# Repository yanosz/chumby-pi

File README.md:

# Turn a Raspberry Pi into a Chumby

> **Heads up:** this is an AI-generated hobby project, built for fun and
> not actively maintained. No support and no warranty — but it works, and
> it's yours to tinker with.

Remember the [Chumby](https://en.wikipedia.org/wiki/Chumby)? The little
squeezable Wi-Fi gadget that showed widgets and woke you up in the
morning, until its servers went dark. This project brings its control
panel back to life on a Raspberry Pi with a small touchscreen — running
the **real** `controlpanel.swf` from the original firmware, unmodified.

It does that with [chumby-ruffle](https://github.com/yanosz/chumby-ruffle),
a fork of the [Ruffle](https://ruffle.rs) Flash player that pretends to be
Chumby hardware. The panel never notices the difference: the clock ticks,
alarms ring, internet radio streams, and your volume and settings stick
around between reboots.

## What you'll need

- A **Raspberry Pi with a small touchscreen.** The reference build is a
  Pi 3B+ with a 3.5″ SPI display and a USB audio dongle; other displays
  and sound devices work too — see [docs/hardware.md](docs/hardware.md).
- The **Chumby firmware files** — `controlpanel.swf`, the intro, and
  the alarm tones. These are copyrighted and **not included here**:
  pull them from your own Chumby's backup, or let
  `chumby-download-firmware` (part of the package) fetch them all from
  Chumby's still-running servers — it asks first and shows what it
  downloads. Widgets are optional; without any, the panel is a clock.
  Which file goes where is in [docs/setup.md](docs/setup.md).

## Try it on your computer first

Before touching the Pi, you can run the panel in a window on any Linux
machine:

```sh
git clone --recursive https://github.com/yanosz/chumby-pi.git
cd chumby-pi
# drop controlpanel.swf into ruffle/swf-assets/ first — see docs/setup.md
cd ruffle && cargo build -p ruffle_desktop
./run-controlpanel.sh
```

Your PC has no bend sensor (the squeeze the Chumby is famous for), so
long-press with the mouse to fake it.

## Put it on the Pi

The full walkthrough — flashing the card, installing the packages, and
setting up the boot-to-panel kiosk — lives in
**[docs/setup.md](docs/setup.md)**. Follow it to the end and the Pi boots
straight into the control panel, no desktop in sight.

## The display (SPI TFT)

The reference display is a 3.5″ 480×320 ILI9486 SPI panel with XPT2046
resistive touch — sold as "Waveshare 3.5inch RPi LCD (B)" and as many
clones. Two things matter:

- **Skip the vendor's driver instructions.** Overlays like
  `waveshare35b-v2` (and the wiki's `hdmi_*` block) use the old fbtft
  framebuffer driver, which Wayland cannot see — the kiosk then fails
  with *"Found 0 GPUs, cannot create backend"*. The mainline kernel
  already ships a proper DRM driver for this panel.
- Append this to `/boot/firmware/config.txt` and reboot:

  ```
  dtparam=spi=on
  dtoverlay=piscreen,speed=24000000,rotate=0,drm,swapxy=on,invy=on
  ```

  `drm` selects the mainline driver; `swapxy` and `invy` align the
  touchscreen axes with the landscape screen.

That's all: the kiosk finds the SPI panel by itself, on any Pi model.
**HDMI and DSI displays** (like the official 7″ touchscreen) **need no
configuration at all** — the overlay lines above are only for SPI
panels, which the Pi cannot detect on its own. To pin a specific
display, set `WLR_DRM_DEVICES` in `/etc/default/chumby-player`.

## What's in this repo

| Directory | What's inside |
|-----------|---------------|
| `ruffle/` | the chumby-ruffle player, as a git submodule. It brings its own `fixtures/` (the fake Chumby the panel talks to), the desktop launcher, and where the copyrighted firmware files go |
| `pkg/` | the Debian packages and the kiosk service that boots to the panel |
| `docs/` | the setup and hardware guides — **start with [docs/setup.md](docs/setup.md)** |

There's also a `claude-docs/` folder with the engineering record — what
this thing has to do, how it's put together, and how to work on it. Handy
if you want to know *why* something works, but not needed to use it. The
player has its own record, in the `ruffle/` submodule.

A `yoga-widget/` folder, where present, is a separate project — chumby-yoga,
a video widget for the original chumby hardware. It is not part of this repo
(ignored here) and is documented in its own repository.

Likewise `rust-remote/` (chumby-rust-remote): a separate project with its own git
repository, a small service for the original chumby hardware that switches
night mode and keeps the chumby awake. Ignored here, documented in its own README.

## What works, and what doesn't

**Working on the Pi:** boot-to-panel kiosk with the original boot
animation, the clock, touch input (long-press = squeeze), alarms with a
backup beep if the player should die, My-Streams internet radio, music
from a USB stick, your own widgets, volume and mute, brightness and
night mode on displays with a kernel backlight — all with settings that
persist across reboots. The player restarts itself after a crash, a
clock correction or a network outage. Opt-in: chumby.com's still-alive
radio directories, device registration and your account's widget
channels.

**Out of scope:** the panel's social surface (widget browsing, rating,
sending), the timezone and network screens (the Pi OS owns those), and
anything that needs chumby hardware the Pi lacks.

## A note on sharing

The firmware files stay yours: they are chumby's, never commit or
redistribute them. Everything else here (scripts, fixtures, and docs)
is under Ruffle's Apache-2.0 / MIT licenses.

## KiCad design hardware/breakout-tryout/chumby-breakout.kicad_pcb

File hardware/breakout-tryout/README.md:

# chumby-breakout — generated KiCad tryout

A **skills tryout, not the engineering record**: the issue-2 breakout
board (claude/issues.md) generated end-to-end by script, 2026-07-17.
The folder is gitignored. Decisions still open in issue 2 (P50V
beep-out, power switch, HP_NOTIN, cable-end housing) are baked in here
as assumptions — do not fab from this.

**2026-07-19: gen_sch.py's P1 net map is known wrong** — it inherits a
one-row misread of the schematic, since corrected by measurement
(`../chumby-hat/accelerometer.md` §3: reset = sch 9↔11, bend line =
sch 17). Regenerate only after taking the corrected table.

- `gen_sch.py` → `chumby-breakout.kicad_sch` — symbols pulled from the
  stock KiCad 9 libs, nets as global labels at computed pin endpoints.
  **ERC: 0 violations** (`--severity-all`).
- `gen_pcb.py` → `chumby-breakout.kicad_pcb` — placement plus a small
  two-layer channel router (vertical escapes on F.Cu, one horizontal
  channel per net on B.Cu, topologically ordered to avoid crossing
  conflicts), GND pours both sides, plated GND mounting holes, silk.
  **DRC: 0 errors, 0 unconnected**; warnings remaining: silk overlaps
  near J6, and the holes-co-located notice inherent to the
  `_Pad_Via` mounting-hole footprint.
- `chumby-breakout-sch.pdf`, `render-top.png`, `render-bottom.png`,
  `gerbers/` — exported views.

Regenerate: `python3 gen_sch.py && kicad-cli sch export netlist
--format kicadxml -o netlist.xml chumby-breakout.kicad_sch &&
python3 gen_pcb.py`.

Board: 100×55 mm. Top edge: P1 chumbilical (2×13 IDC), J3 USB-A
power-out to the Pi. Bottom edge: J2 (2×5 to Pi pins 17–26), J7
speakers (PH2.0 footprint), J6 headphone screw terminal, J4/J5 USB-A
males to the hub (data+GND only, VBUS open by design).

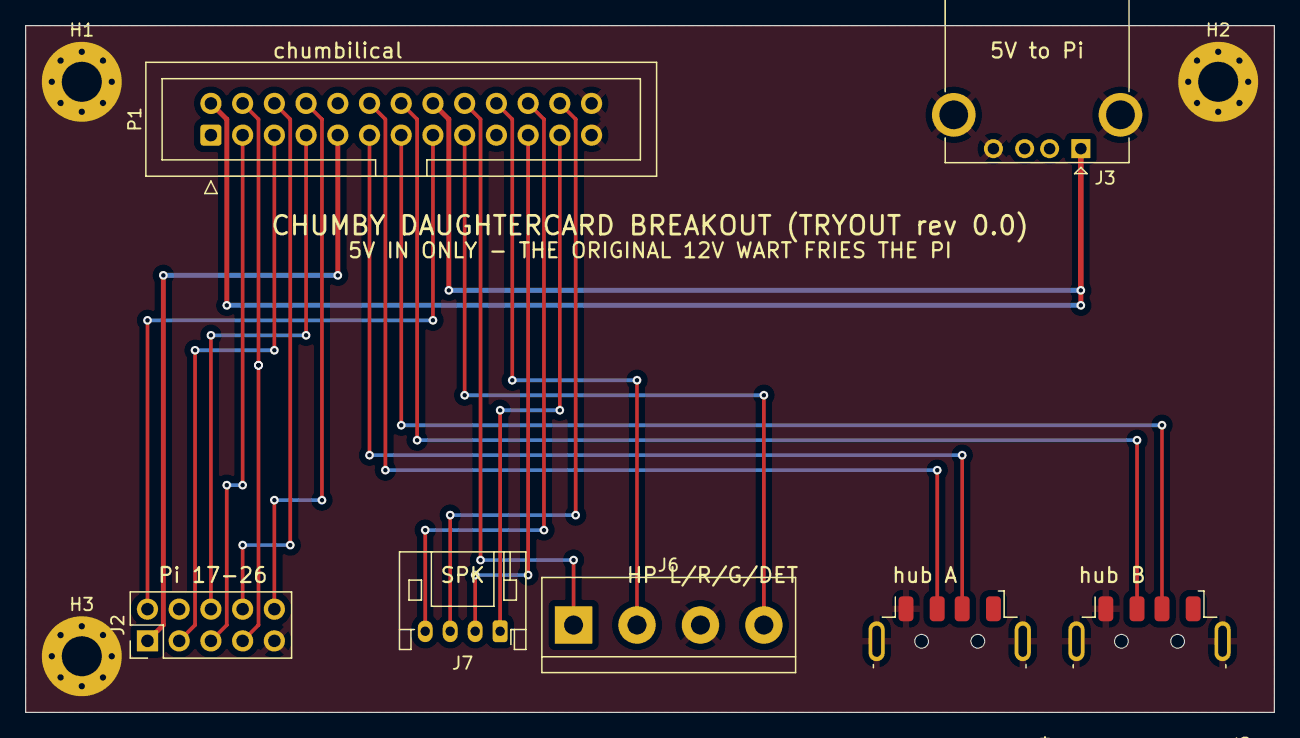
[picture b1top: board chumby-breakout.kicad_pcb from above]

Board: 2 copper layers, 100.0 x 55.0 mm, 10 parts (0 on the bottom side), 21 nets.

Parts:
H1, H2, H3: MountingHole_3.2mm_M3_Pad_Via
J2: PinHeader_2x05_P2.54mm_Vertical
J3: USB_A_Kycon_KUSBX-AS1N-B_Horizontal
J4, J5: USB_A_Molex_48037-2200_Horizontal
J6: TerminalBlock_bornier-4_P5.08mm
J7: JST_PH_S4B-PH-K_1x04_P2.00mm_Horizontal
P1: IDC-Header_2x13_P2.54mm_Vertical

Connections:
+3V3: J2.1, P1.9
+5V: J3.1, P1.2, P1.16
CHUMBY_BEND: J2.2, P1.15
CHUMBY_RESET_REQ: J2.6, P1.7
CSPI1_MISO: J2.5, P1.3
CSPI1_MOSI: J2.3, P1.5
CSPI1_SCLK: J2.7, P1.4
CSPI1_SS0: J2.8, P1.6
CSPI1_SS1: J2.10, P1.8
GND: H1.1, H2.1, H3.1, J2.4, J2.9, J3.4, J3.5, J4.4, J4.5, J5.4, J5.5, J6.3, P1.25, P1.26
HPLEFT: J6.1, P1.18
HPRIGHT: J6.2, P1.20
HP_NOTIN: J6.4, P1.17
SPKL_VO1: J7.1, P1.23
SPKL_VO2: J7.2, P1.21
SPKR_VO1: J7.3, P1.24
SPKR_VO2: J7.4, P1.22
USBB2_DN: J5.2, P1.13
USBB2_DP: J5.3, P1.14
USBB_DN: J4.2, P1.11
USBB_DP: J4.3, P1.12
